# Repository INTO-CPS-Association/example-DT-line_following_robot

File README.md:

# case-study_line_follower_robot

## Case Study Description

This example, originally developed in the DESTECS project. The model simulates a robot that can follow a line painted on the ground. The line contrasts from the background and the robot uses a number of sensors to detect light and dark areas on the ground. The robot has two wheels, each powered by individual motors to enable the robot to make controlled changes in direction. The number and position of the sensors may be configured in the model. A controller takes input from the sensors and encoders from the wheels to make outputs to the motors. 

The robot moves through a number of phases as it follows a line. At the start of each line is a specific pattern that will be known in advance. Once a genuine line is detected on the ground, the robot follows it until it detects that the end of the line has been reached, when it should go to an idle state. 

## Example Artefacts Overview

The example is available at https://github.com/into-cps/case-study_line_follower_robot in the *master* branch. There are several subfolders for the various elements: DSEs - contains various work in progress DSE scripts to alter CT and DE parameters ; FMU - contains the various FMUs of the study; Models - contains the constituent models defined using the INTO-CPS simulation technologies; Multi-models - contains the multi-model definitions and co-simulation configurations - with 3D and non-3D options, and also with and without the use of replicated FMUs; SysML - contains the SysML models defined for the study; resources - various images for the purposes of this readme file; and userMetricScripts - contains files for DSE analysis. 

The case-study_line_follower_robot folder can be opened in the INTO-CPS application to run the various co-simulations as detailed in this document.

## INTO-CPS Technology

### INTO SysML profile

The multi-model architecture, defined in the INTO-CPS SysML profile, splits the original model into three subsystems, as shown in  the Architecture Structure Diagram. This version comprises *Body* and *Sensor* subsystems and a *Controller* cyber component. The *Body* subsystem, with a target platform as 20-sim as a CT model, comprises the Body, Encoder, Wheel and Motor components. The *Sensor* subsystem contains only Sensor components. The *Controller* component remains the same as the original SysML model. 

Connections are made between the different subsystems, and the underlying components realising the source and destination of values. Two connection diagrams are defined for two block instances *robot2sensor* and *3DRobot*. The first, shown below connects the controller, body and sensor instances:

The second block instance, *3DRobot*, includes a 3DVisualisation block. The other connections remain the same as in the  *robot2sensor* instance.

### Models 

The multi-model produced and analysed using INTO-CPS technology stems from the baseline Crescendo co-model. The multi-model comprises 4 models, splitting the Crescendo model into a multi-CT model, with a single DE model. 

The Crescendo elements (a VDM-RT controller and a 20-sim plant) are largely unchanged, modified so that the 20-sim model is partitioned into 3 high-level submodels: a *body* and two models for the robot *sensors*. By modelling in this way, each submodel can be exported as a separate FMU. For the purposes of multi-modelling, we concentrate on the 20-sim Body subsystem which does not contain the sensors. In their place, the body submodel contains ports for the robot position: **robot_x**, **robot_y**, **robot_z** and **robot_theta**. The other ports  are the same as in the baseline Crescendo model (**total_energy_used**, **servo_left_input** and **servo_right_input**, **wheel_left_rotation** and **wheel_right_rotation**) for interfacing with the controller and visualisation models. The Sensor model contains a link to the map and models a single sensor, taking inputs related to the robot position (**robot_x**, **robot_y**, **robot_z** and **robot_theta**) and returning the current sensor reading(**lf_1_sensor_reading**). 

The VDM-RT controller model is unchanged from the original Crescendo controller.

An OpenModelica model has been defined to model the robot sensors - an alternative to the 20-sim sensor model - this model has the same port collection as the 20-sim version.

### Multi-Models

The case study has two multi-models, one without and one with 3D visualisation (*lfr-1* and *lfr-2* respectively). The two multi-models share several connections; with the *lfr-2* version having additional connections to the 3D visualisation FMU. 

The first collection of connections is between the Body 20-sim model and the Controller VDM-RT model. In this collection, there are several connections corresponding to signals for the actuators that power the motors for the wheels:
- from the *Controller* **servo_left** variable of type real to the **servo_left_input** port of the *Body*; and
- from the *Controller* **servo_right** variable of type real to the **servo_right_input** port of the *Body*

The second collection of connections is present between the Sensor models and the Controller VDM-RT model. For each sensor there is one connection to the controller to represent inputs from line-following sensors that can detect areas of light and dark on the ground. Therefore for a two-sensor model there are two connections:
- from the *Sensor1* **lf_1_sensor_reading** port to the *Controller* **lfLeftVal** port; and 
- from the *Sensor2* **lf_1_sensor_reading** port to the *Controller* **lfRightVal** port. 

A third collection of connections exist between the body and the sensors related to the robot position:
- from the *Body* **robot_x** port to the *Sensor1* and *Sensor2* **robot_x** port; 
- from the *Body* **robot_y** port to the *Sensor1* and *Sensor2* **robot_y** port; 
- from the *Body* **robot_z** port to the *Sensor1* and *Sensor2* **robot_z** port; and 
- from the *Body* **robot_theta** port to the *Sensor1* and *Sensor2* **robot_theta** port. 

Four design parameters are present also: the separation of the line-following sensors from the centre line, in metres (**sensor1.lf_position_x** and **sensor2.lf_position_x**); and the distance forward of the line-following sensors from the centre of the robot, in metres (**sensor1.lf_position_y** and **sensor2.lf_position_y**).

The final collection of connections are only present in the *lfr-2* multi-model, enabling 3D visualisation:
- from the *Body* **robot_x** port to the *3D* **animation.robot.position.x** port; 
- from the *Body* **robot_y** port to the *3D* **animation.robot.position.y** port; 
- from the *Body* **robot_theta** port to the *3D* **animation.robot.angle.z** port;
- from the *Sensor1* **lf_1_sensor_reading** port to the *3D* **animation.sensor.lf.left.reading** port; and
- from the *Sensor2* **lf_1_sensor_reading** port to the *3D* **animation.sensor.lf.left.reading** port.

### Co-simulation

For both the *lfr-1* and *lfr-2* multi-models, co-simulations require approximately 25-30 seconds of simulation to traverse the full map, using a step size of 0.01 seconds. 

### Analyses and Experiments

Below we detail some useful experiments to demonstrate features of the INTO-CPS tool chain.

#### Change FMUs/parameters

The case study has several Sensor FMUs. In the multi-model configuration it is possible to swap the FMU allocated to each sensor instance of the multi-model. We can therefore compare the results of co-simulation using 20-sim sensors (*Sensor_Block.fmu*) for OpenModelica sensors (**To appear**), or a combination of the two. 

In addition, there are parameters defined for the two sensors: an x and y position **lf_position_x** and **lf_position_y**. Experiments may be carried out by defining different values for these to model different placement of the sensors on the robot. 

#### Simulations due to previous results 

Simulations can be replayed using different design parameter values to change the position of the robot sensors. Changing these parameters amounts to changing the design of the robot - some value pairs will produce robots which perform in some way better (e.g. have a faster lap time) and others will result in robots which can not follow the line.

#### Design Space Exploration

TBD
=======
# example-DT-line_following_robot
This example demonstrates transmission of data from a deployed line following robot, a correlated detection of its postion on a track via a camera and image recognition, and making it available in a co-simulation with its digital twin.

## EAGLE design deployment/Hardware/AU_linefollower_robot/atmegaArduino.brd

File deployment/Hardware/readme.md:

# Hardware overview

The new linefollower robot is made up of 3 boards:

1. An Arduino Uno that drives the servos and is connected to the sensors. It is controllable using I2C or GPIO PINS based on the hardware switch which desides the mode.
2. An ATMega128P which is also connected to the sensors and has two GPIO connected to the Arduino for simple control of the servos
3. An Raspberry PI that is connected though a level converter to the Arduino I2C where it reads the sensors and sets the PWM signals for the servos

Due to the high power load batteries (4 pices) does not last very long, and control will be schetcy when power is running low.

Currently there is not a good way to power the robot directly from a wall socket.

It would be good to upgrade the power supply such that the external power connector that feds power to the battery rail could be connected to a 12V power supply delivering sufficient power to the Arduino (which can handle 12V) however a e.g. 2A DC Step Down 5V Voltage Regulator Power Supply Converter module from 12v. This way everything will have more than enough power. The Arduino can not be powered by 5V from a USB charger since it requires 9-12V.

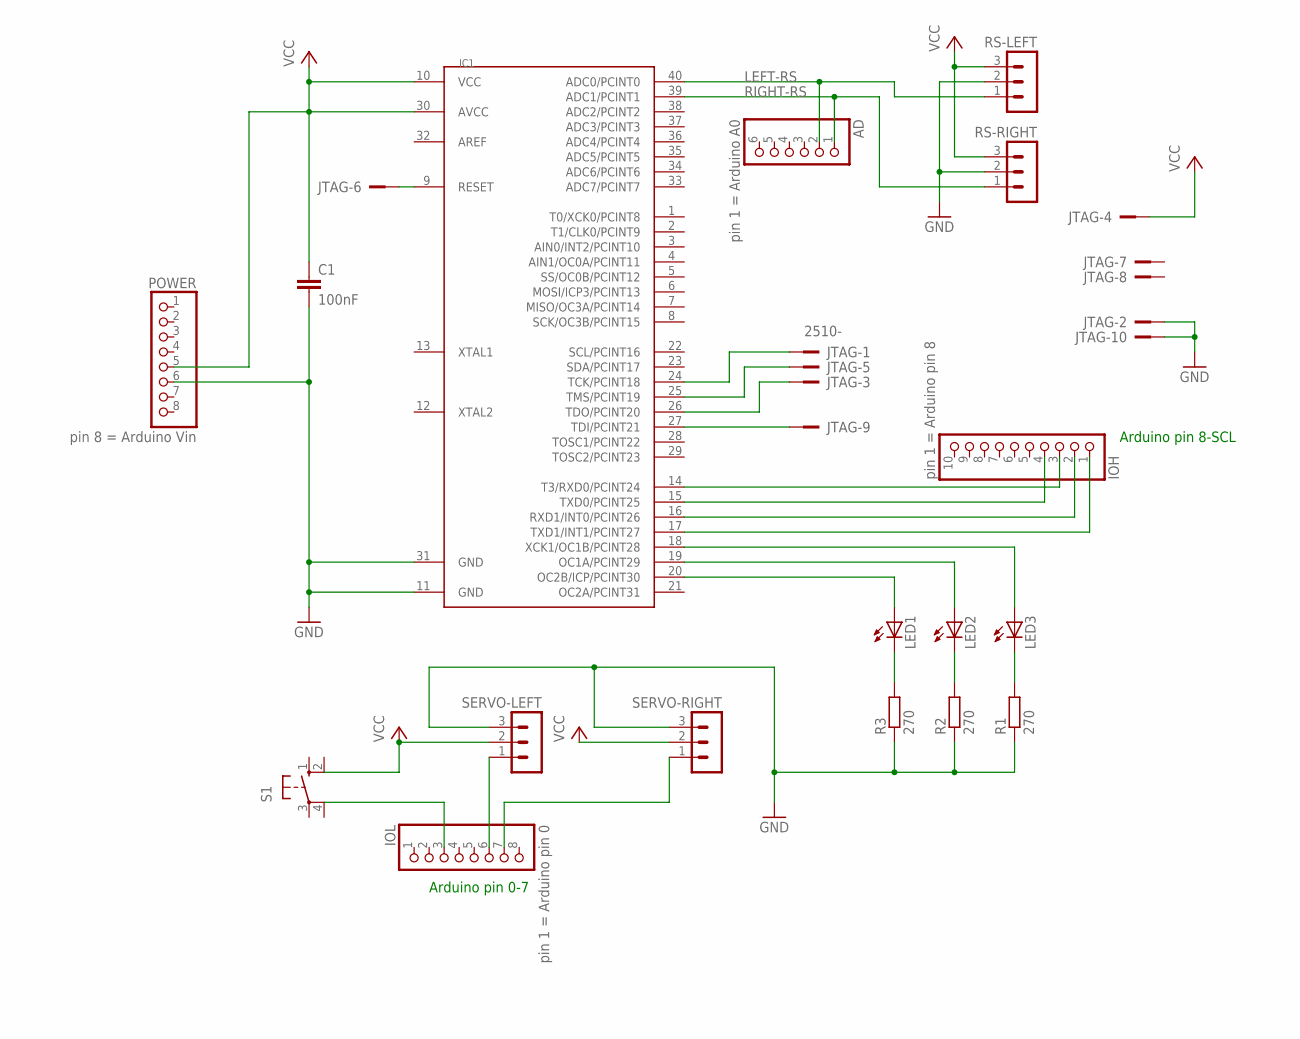
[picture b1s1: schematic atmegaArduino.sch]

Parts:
AD: pin 1 = Arduino A0; 1X06/90
C1: 100nF; C050-025X075
IC1: MEGA1284P; DIL40
IOH: pin 1 = Arduino pin 8; 1X10/90
IOL: pin 1 = Arduino pin 0; 1X08/90
JTAG: 2510-; PAK100/2500-10
LED1, LED2, LED3: LED_ELD260; LED_LD260
POWER: pin 8 = Arduino Vin; 1X08/90
R1, R2, R3: 270; 0204/5
RS-LEFT: MA03-1
RS-RIGHT: MA03-1
S1: 10-XX; B3F-10XX
SERVO-LEFT: MA03-1
SERVO-RIGHT: MA03-1

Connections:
GND: C1.2, IC1.11 (GND), IC1.31 (GND), JTAG.2, JTAG.10, POWER.6, R1.1, R2.1, R3.1, RS-LEFT.2, RS-RIGHT.2, SERVO-LEFT.3, SERVO-RIGHT.3
LEFT-RS: AD.2, IC1.40 (ADC0/PCINT0), RS-LEFT.1
unnamed: IC1.14 (T3/RXD0/PCINT24), IOH.3
unnamed: IC1.15 (TXD0/PCINT25), IOH.4
unnamed: IC1.24 (TCK/PCINT18), JTAG.1
unnamed: IC1.25 (TMS/PCINT19), JTAG.5
unnamed: IC1.26 (TDO/PCINT20), JTAG.3
unnamed: IOL.7, SERVO-RIGHT.1
unnamed: IC1.27 (TDI/PCINT21), JTAG.9
unnamed: IOL.6, SERVO-LEFT.1
unnamed: LED1.K (C), R3.2
unnamed: LED2.K (C), R2.2
unnamed: IC1.9 (RESET), JTAG.6
unnamed: LED3.K (C), R1.2
unnamed: IC1.20 (OC2B/ICP/PCINT30), LED1.A
unnamed: IC1.19 (OC1A/PCINT29), LED2.A
unnamed: IC1.18 (XCK1/OC1B/PCINT28), LED3.A
unnamed: IC1.16 (RXD1/INT0/PCINT26), IOH.2
unnamed: IC1.17 (TXD1/INT1/PCINT27), IOH.1
RIGHT-RS: AD.1, IC1.39 (ADC1/PCINT1), RS-RIGHT.1
VCC: C1.1, IC1.10 (VCC), IC1.30 (AVCC), JTAG.4, POWER.5, RS-LEFT.3, RS-RIGHT.3, SERVO-LEFT.2, SERVO-RIGHT.2

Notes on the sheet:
Arduino pin 0-7
Arduino pin 8-SCL

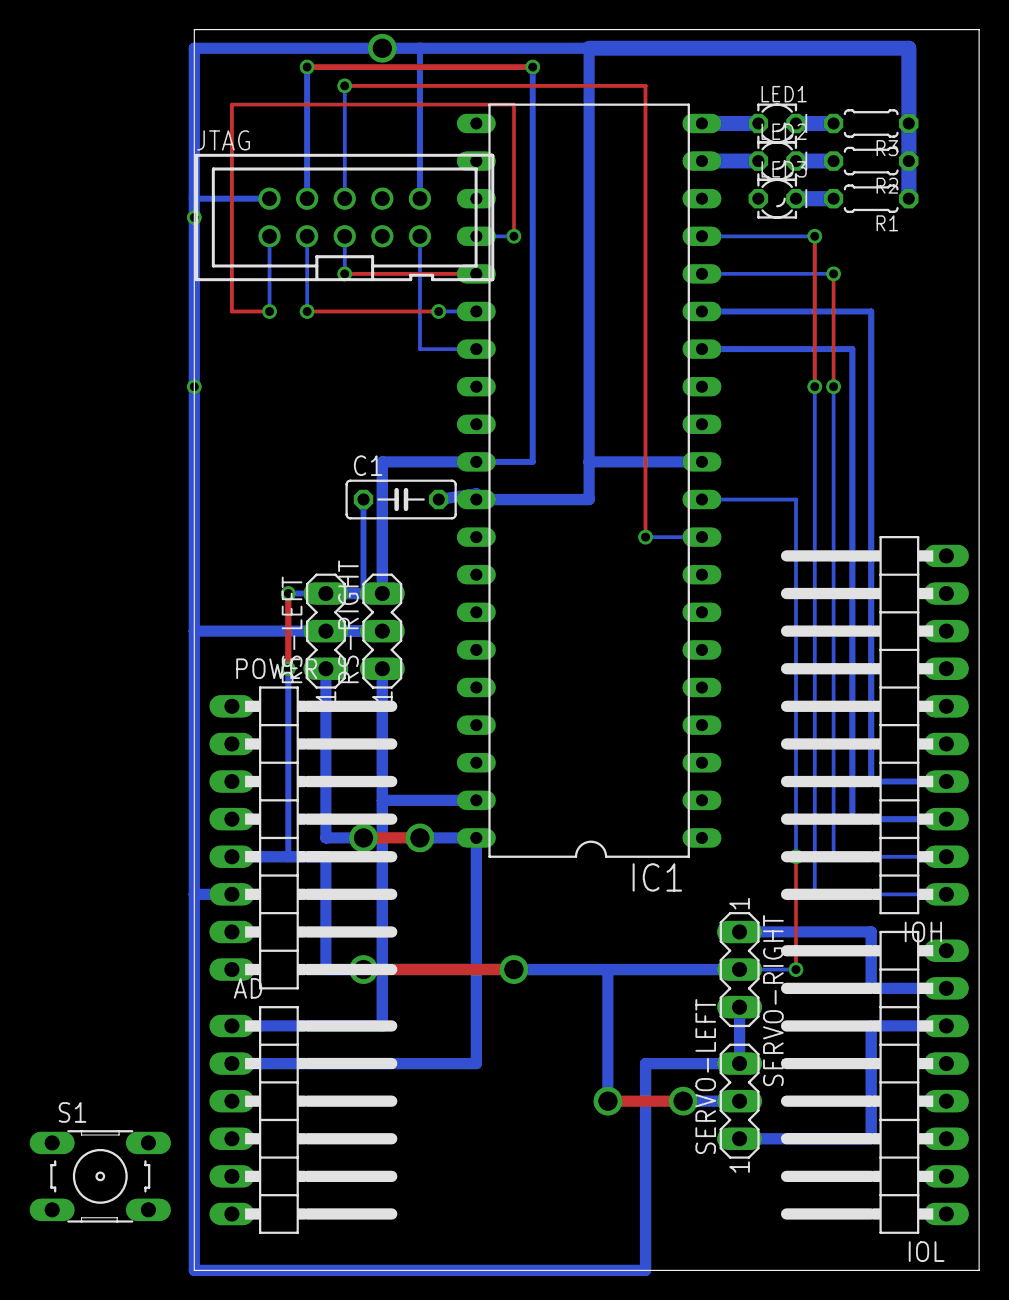
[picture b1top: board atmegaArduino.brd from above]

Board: 2 copper layers, 53.0 x 83.8 mm, 18 parts (0 on the bottom side), 21 nets.

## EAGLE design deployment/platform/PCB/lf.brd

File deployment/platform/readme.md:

# Robot Platform

The Robot platform is using the Arduino Mega 2560 controller board [link](https://www.ebay.com/itm/MEGA-2560-R3-ATMEGA16U2-ATMEGA2560-16AU-Board-Free-USB-Cable-For-Arduino/272386431938?hash=item3f6b7f1bc2:g:cycAAOSwLF1X4~Zt:rk:3:pf:0) and a standard cheap eBay 2WD line following robot platform.

## Hardware

* High Quality Plastic Battery Holder Storage Box Case for 18650 With Wire Lead 8 kr [Link](https://www.ebay.com/itm/High-Quality-Plastic-Battery-Holder-Storage-Box-Case-for-18650-With-Wire-Lead-FR/122357752996?hash=item1c7d1724a4:g:JK8AAOSw4A5YpR0Z:rk:2:pf:0)

* L298N Dual H Bridge DC Stepper Motor Drive Controller Board Module For Arduino - 21 kr [Link](https://www.ebay.com/itm/Stepper-Motor-Drive-Controller-Board-Module-L298N-Dual-H-Bridge-DC-For-Arduino/170926726867?epid=1141772933&hash=item27cc06ded3:g:s4wAAOSwXeJXe31g:rk:1:pf:0)

* New Smart Motor Robot Car Battery Box Chassis Kit Speed Encoder For Arduino 52 kr [Link](https://www.ebay.com/itm/2WD-New-Motor-Smart-Robot-Car-Chassis-Kit-Speed-Encoder-Battery-Box-For-Arduino/282778413895?hash=item41d6e82b47:g:mkIAAOSwk1haKS3X:rk:1:pf:0)

* 3 Series BMS PCB Placa de Protección para Batería de Litio 18650 33 kr [Link](https://www.ebay.com/itm/Proteccion-cargador-placa-PCB-BMS-Modulo-Para-18650-Pila-Litio-Bateria/263595449713?hash=item3d5f835d71:m:mFyWpbIf34v8YofUjUjuEaQ:rk:1:pf:0) CHOOSE: 3S 12V 10A

* 3 Panasonic NCR18650GA 3,6V / 3450mAh - Max 10A 150 kr [link](https://www.ebay.com/itm/4X-3450mAh-10A-GENUINE-SANYO-PANASONIC-NCR18650GA-Tested-Cells-18650/173615458719?hash=item286c49a99f:m:meh9BLsrThH0GlbX65FeLTA:rk:1:pf:0)

* (optional) 5PCS Slot Type IR Optocoupler Speed Sensor Module LM393 for Arduino 14 kr [link](https://www.ebay.com/itm/5PCS-Slot-Type-IR-Optocoupler-Speed-Sensor-Module-LM393-for-Arduino/132478779559?hash=item1ed859c0a7:g:disAAOSw0lVbCTU0:rk:1:pf:0)

* 5PCS IR Infrared Line Track Follower Sensor TCRT5000 Obstacle Avoidanc 12 kr [link](https://www.ebay.com/itm/5PCS-TCRT5000-IR-Infrared-Line-Track-Follower-Sensor-Obstacle-Avoidanc-Module/311568146310?epid=911730611&hash=item488ae89f86:g:TDUAAOSwlzZbIiiI:rk:1:pf:0)

* (optional) 2PCS Obstacle Avoidance TCRT5000 Infrared Track Sensor Module For Arduino 7 kr [link](https://www.ebay.com/itm/2-5-10PCS-Obstacle-Avoidance-TCRT5000-Infrared-Track-Sensor-Module-For-Arduino/401397862776?hash=item5d752d5178:m:m6xu1VawCBR2mbT-hgp2_Gw:rk:1:pf:0) CHOOSE 2pcs

* 3d printed parts

* cables

* Arduino MEGA Sensor Shield. [Gerber files](PCB/gerber.zip)

### Sensor Front Mount

The mount should be 20 mm high i.e. the distance from under the robot frame to where the sensors are screwed into the mount.

[Sensor Mount STL](LF_sensor_holder.stl)

## Controller wiring

## Assembled robot

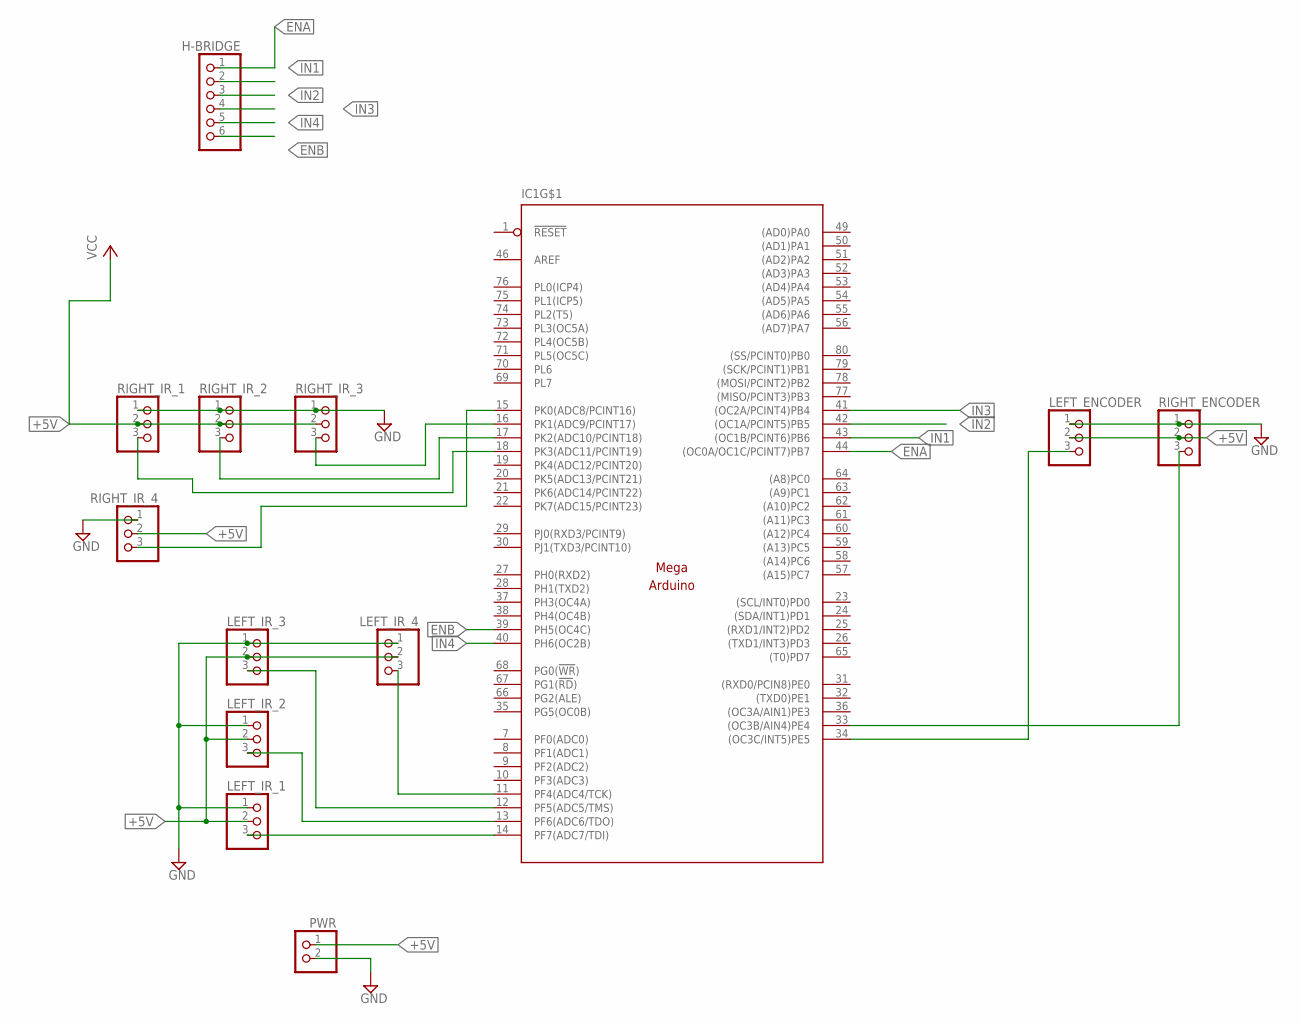
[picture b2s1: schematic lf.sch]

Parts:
H-BRIDGE: PINHD-1X6; 1X06
IC1: MEGAARDUINO_22; MEGA_ARDUINO_2
LEFT_ENCODER: PINHD-1X3; 1X03
LEFT_IR_1, LEFT_IR_2, LEFT_IR_3, LEFT_IR_4: PINHD-1X3; 1X03
PWR: PINHD-1X2; 1X02
RIGHT_ENCODER: PINHD-1X3; 1X03
RIGHT_IR_1, RIGHT_IR_2, RIGHT_IR_3, RIGHT_IR_4: PINHD-1X3; 1X03

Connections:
+3V3: IC1.2 (+3V3)
+5V: IC1.3 (+5V), IC1.47 (+5V), IC1.48 (+5V), LEFT_ENCODER.2, LEFT_IR_1.2, LEFT_IR_2.2, LEFT_IR_3.2, LEFT_IR_4.2, PWR.1, RIGHT_ENCODER.2, RIGHT_IR_1.2, RIGHT_IR_2.2, RIGHT_IR_3.2, RIGHT_IR_4.2
+VIN: IC1.6 (+VIN)
ENA: H-BRIDGE.1, IC1.44 ((OC0A/OC1C/PCINT7)PB7)
ENB: H-BRIDGE.6, IC1.39 (PH5(OC4C))
GND: IC1.4 (GND), IC1.5 (GND), IC1.45 (GND), IC1.81 (GND), IC1.82 (GND), LEFT_ENCODER.1, LEFT_IR_1.1, LEFT_IR_2.1, LEFT_IR_3.1, LEFT_IR_4.1, PWR.2, RIGHT_ENCODER.1, RIGHT_IR_1.1, RIGHT_IR_2.1, RIGHT_IR_3.1, RIGHT_IR_4.1
IN1: H-BRIDGE.2, IC1.43 ((OC1B/PCINT6)PB6)
IN2: H-BRIDGE.3, IC1.42 ((OC1A/PCINT5)PB5)
IN3: H-BRIDGE.4, IC1.41 ((OC2A/PCINT4)PB4)
IN4: H-BRIDGE.5, IC1.40 (PH6(OC2B))
unnamed: IC1.16 (PK1(ADC9/PCINT17)), RIGHT_IR_3.3
unnamed: IC1.17 (PK2(ADC10/PCINT18)), RIGHT_IR_2.3
unnamed: IC1.33 ((OC3B/AIN4)PE4), RIGHT_ENCODER.3
unnamed: IC1.34 ((OC3C/INT5)PE5), LEFT_ENCODER.3
unnamed: IC1.14 (PF7(ADC7/TDI)), LEFT_IR_1.3
unnamed: IC1.13 (PF6(ADC6/TDO)), LEFT_IR_2.3
unnamed: IC1.12 (PF5(ADC5/TMS)), LEFT_IR_3.3
unnamed: IC1.18 (PK3(ADC11/PCINT19)), RIGHT_IR_1.3
unnamed: IC1.15 (PK0(ADC8/PCINT16)), RIGHT_IR_4.3
unnamed: IC1.11 (PF4(ADC4/TCK)), LEFT_IR_4.3

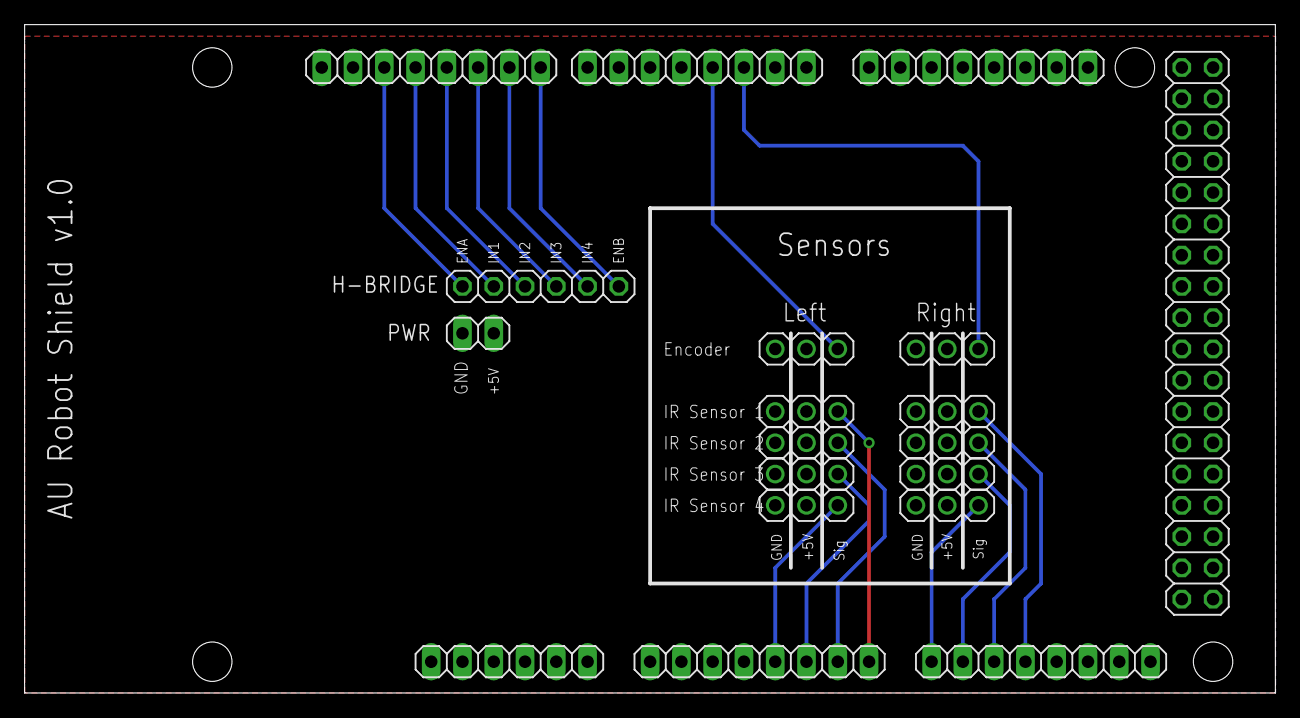
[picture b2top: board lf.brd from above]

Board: 2 copper layers, 101.6 x 54.3 mm, 13 parts (0 on the bottom side), 18 nets.

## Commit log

2020-01-24 added esp code
2020-01-24 slowed down robot
